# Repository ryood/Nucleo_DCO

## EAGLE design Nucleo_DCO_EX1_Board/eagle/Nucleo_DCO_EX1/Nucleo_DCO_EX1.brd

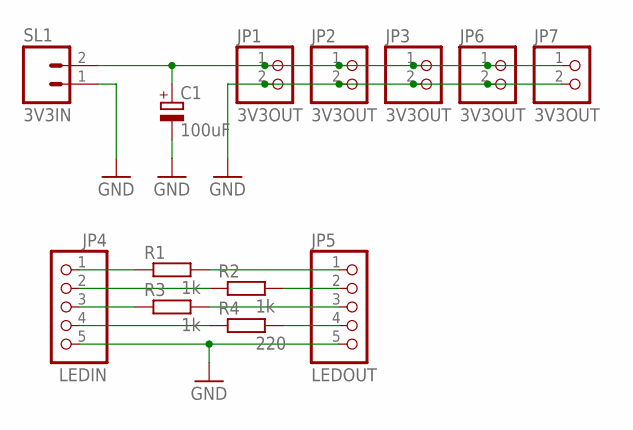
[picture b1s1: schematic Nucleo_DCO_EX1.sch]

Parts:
C1: 100uF; SANYO-OSCON_C6
JP1, JP2, JP3, JP6, JP7: 3V3OUT; 1X02
JP4: LEDIN; 1X05
JP5: LEDOUT; 1X05
R1, R2, R3: 1k; 0207/7
R4: 220; 0207/7
SL1: 3V3IN; 02P

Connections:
GND: C1.-, JP1.2, JP2.2, JP3.2, JP4.5, JP5.5, JP6.2, JP7.2, SL1.1
unnamed: C1.+, JP1.1, JP2.1, JP3.1, JP6.1, JP7.1, SL1.2
unnamed: JP4.1, R1.1
unnamed: JP5.1, R1.2
unnamed: JP4.2, R2.1
unnamed: JP5.2, R2.2
unnamed: JP4.3, R3.1
unnamed: JP5.3, R3.2
unnamed: JP4.4, R4.1
unnamed: JP5.4, R4.2

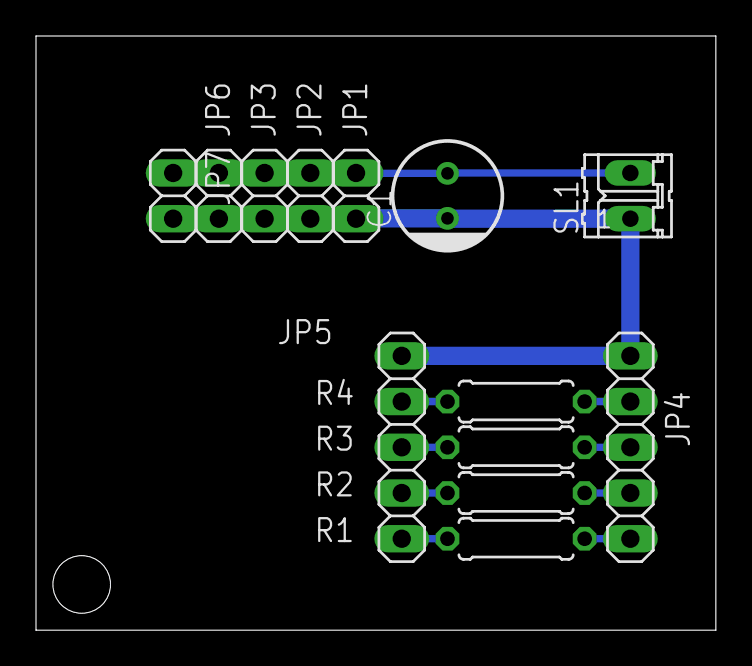
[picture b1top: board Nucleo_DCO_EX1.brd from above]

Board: 2 copper layers, 37.8 x 33.0 mm, 13 parts (0 on the bottom side), 10 nets.

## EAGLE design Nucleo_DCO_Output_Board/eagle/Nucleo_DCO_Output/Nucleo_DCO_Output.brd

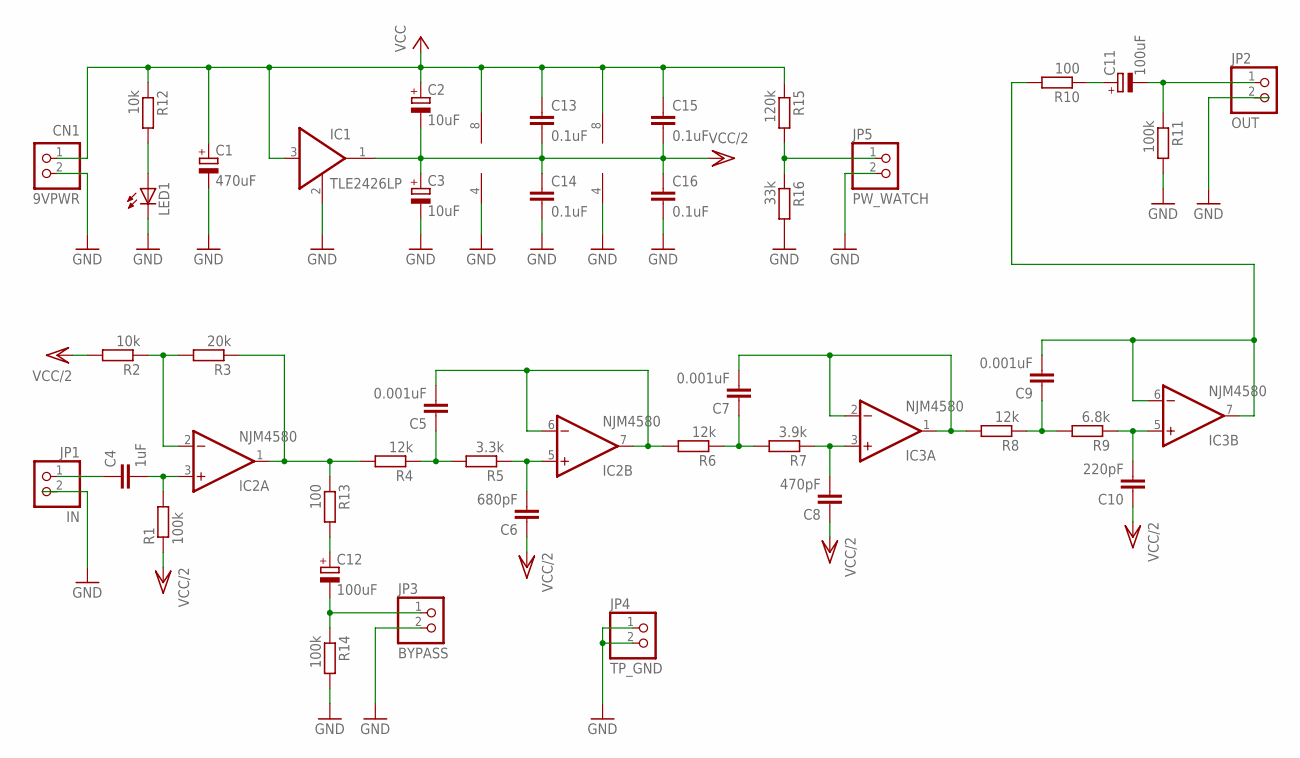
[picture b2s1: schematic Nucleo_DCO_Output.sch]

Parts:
C1: 470uF; SANYO-OSCON_F13
C2, C3: 10uF; E2,5-6
C4: 1uF; C050-035X075
C5, C7, C9: 0.001uF; C050-035X075
C6: 680pF; C050-035X075
C8: 470pF; C050-035X075
C10: 220pF; C050-035X075
C11, C12: 100uF; E5-8,5
C13, C15, C16: 0.1uF; C025-024X044
C14: 0.1uF; C050-024X044
CN1: 9VPWR; B2B-XH-A
IC1: TLE2426LP; TO226AA
IC2, IC3: NJM4580; DIL08
JP1: IN; 1X02
JP2: OUT; 1X02
JP3: BYPASS; 1X02
JP4: TP_GND; 1X02
JP5: PW_WATCH; 1X02
LED1: LED3MM
R1, R11, R14: 100k; 0207/7
R2, R12: 10k; 0207/7
R3: 20k; 0207/7
R4, R6, R8: 12k; 0207/7
R5: 3.3k; 0207/7
R7: 3.9k; 0207/7
R9: 6.8k; 0207/7
R10, R13: 100; 0207/7
R15: 120k; 0207/7
R16: 33k; 0207/7

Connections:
GND: C1.-, C3.-, C14.2, C16.2, CN1.2, IC1.2, IC2.4 (V-), IC3.4 (V-), JP1.2, JP2.2, JP3.2, JP4.1, JP4.2, JP5.2, LED1.K (C), R11.2, R14.2, R16.2
unnamed: IC2.1 (OUT), R3.1, R4.2, R13.1
unnamed: IC2.2 (-IN), R2.1, R3.2
unnamed: C6.2, IC2.5 (+IN), R5.1
unnamed: C4.1, JP1.1
unnamed: C4.2, IC2.3 (+IN), R1.2
unnamed: C5.1, R4.1, R5.2
unnamed: C11.+, R10.1
unnamed: C11.-, JP2.1, R11.1
unnamed: C5.2, IC2.6 (-IN), IC2.7 (OUT), R6.2
unnamed: C8.2, IC3.3 (+IN), R7.1
unnamed: C7.1, R6.1, R7.2
unnamed: LED1.A, R12.2
unnamed: C7.2, IC3.1 (OUT), IC3.2 (-IN), R8.2
unnamed: C10.2, IC3.5 (+IN), R9.1
unnamed: C9.1, R8.1, R9.2
unnamed: C9.2, IC3.6 (-IN), IC3.7 (OUT), R10.2
unnamed: C12.+, R13.2
unnamed: C12.-, JP3.1, R14.1
unnamed: JP5.1, R15.2, R16.1
VCC: C1.+, C2.+, C13.1, C15.1, CN1.1, IC1.3 (I), IC2.8 (V+), IC3.8 (V+), R12.1, R15.1
VCC/2: C2.-, C3.+, C6.1, C8.1, C10.1, C13.2, C14.1, C15.2, C16.1, IC1.1 (O), R1.1, R2.2

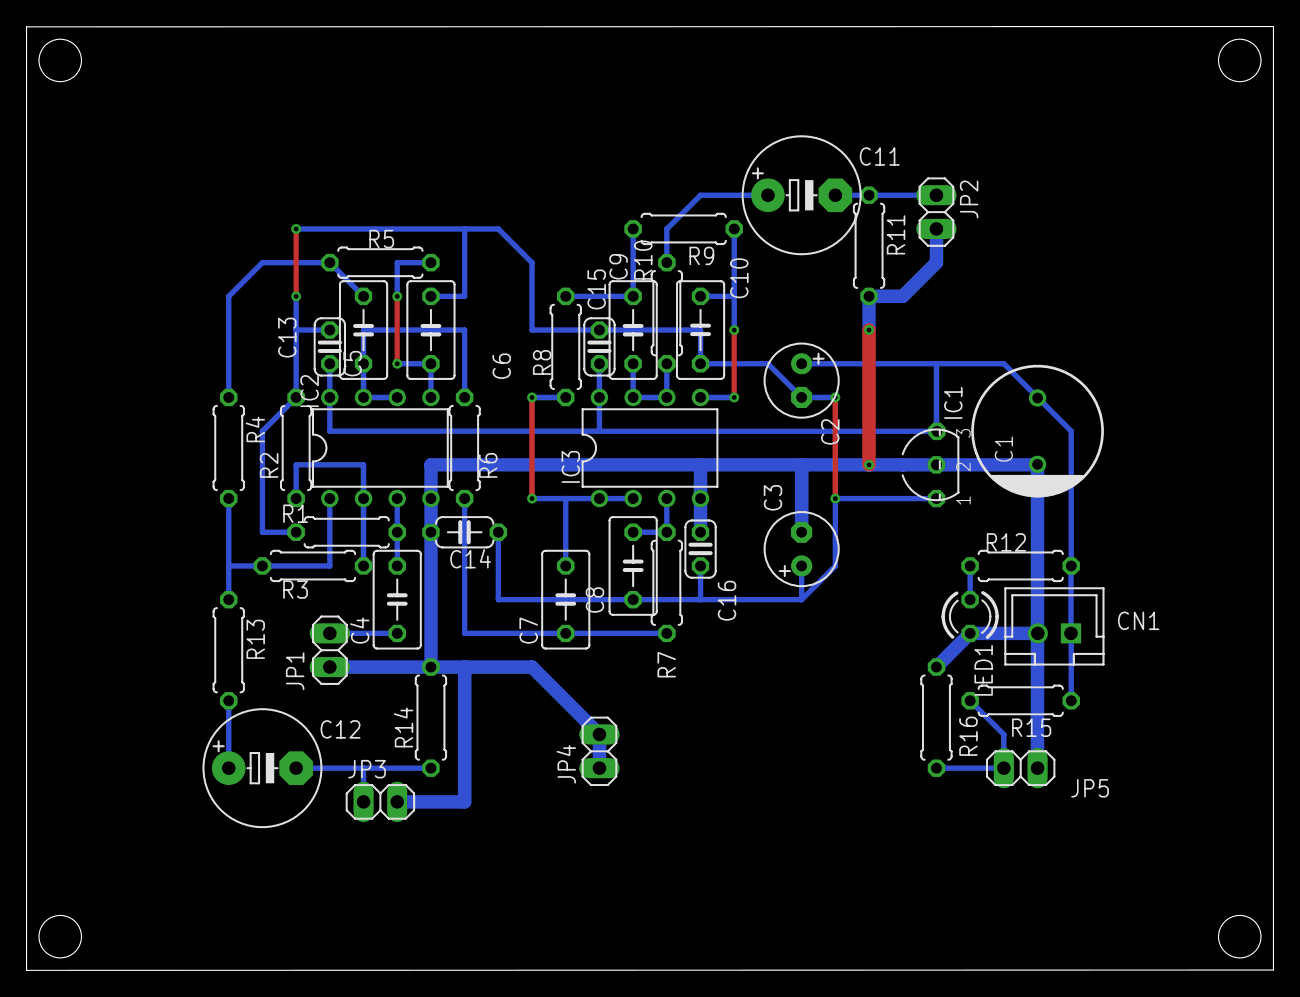
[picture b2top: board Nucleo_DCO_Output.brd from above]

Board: 2 copper layers, 94.0 x 71.1 mm, 42 parts (0 on the bottom side), 22 nets.

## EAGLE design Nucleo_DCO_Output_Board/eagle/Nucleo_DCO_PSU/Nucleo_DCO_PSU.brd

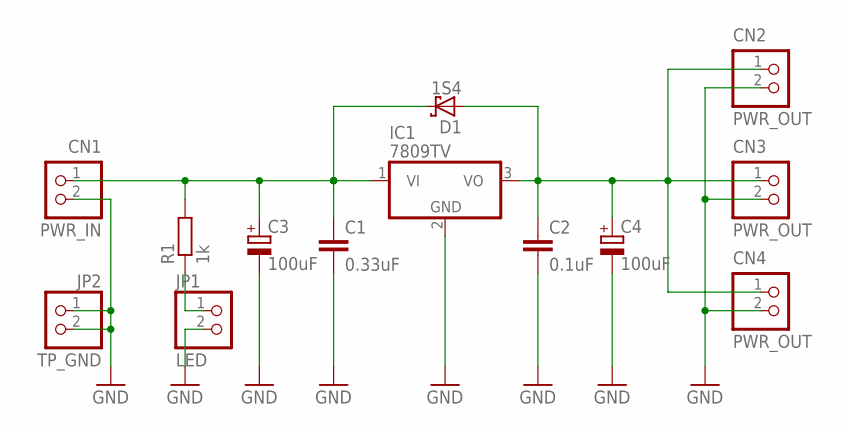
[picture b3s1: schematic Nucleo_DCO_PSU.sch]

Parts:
C1: 0.33uF; C025-024X044
C2: 0.1uF; C025-024X044
C3, C4: 100uF; E5-8,5
CN1: PWR_IN; B2B-XH-A
CN2, CN3, CN4: PWR_OUT; B2B-XH-A
D1: 1S4; DO35-7
IC1: 7809TV; TO220V
JP1: LED; 1X02
JP2: TP_GND; 1X02
R1: 1k; 0207/7

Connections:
GND: C1.2, C2.2, C3.-, C4.-, CN1.2, CN2.2, CN3.2, CN4.2, IC1.2 (GND), JP1.2, JP2.1, JP2.2
unnamed: JP1.1, R1.1
unnamed: C1.1, C3.+, CN1.1, D1.C, IC1.1 (VI), R1.2
unnamed: C2.1, C4.+, CN2.1, CN3.1, CN4.1, D1.A, IC1.3 (VO)

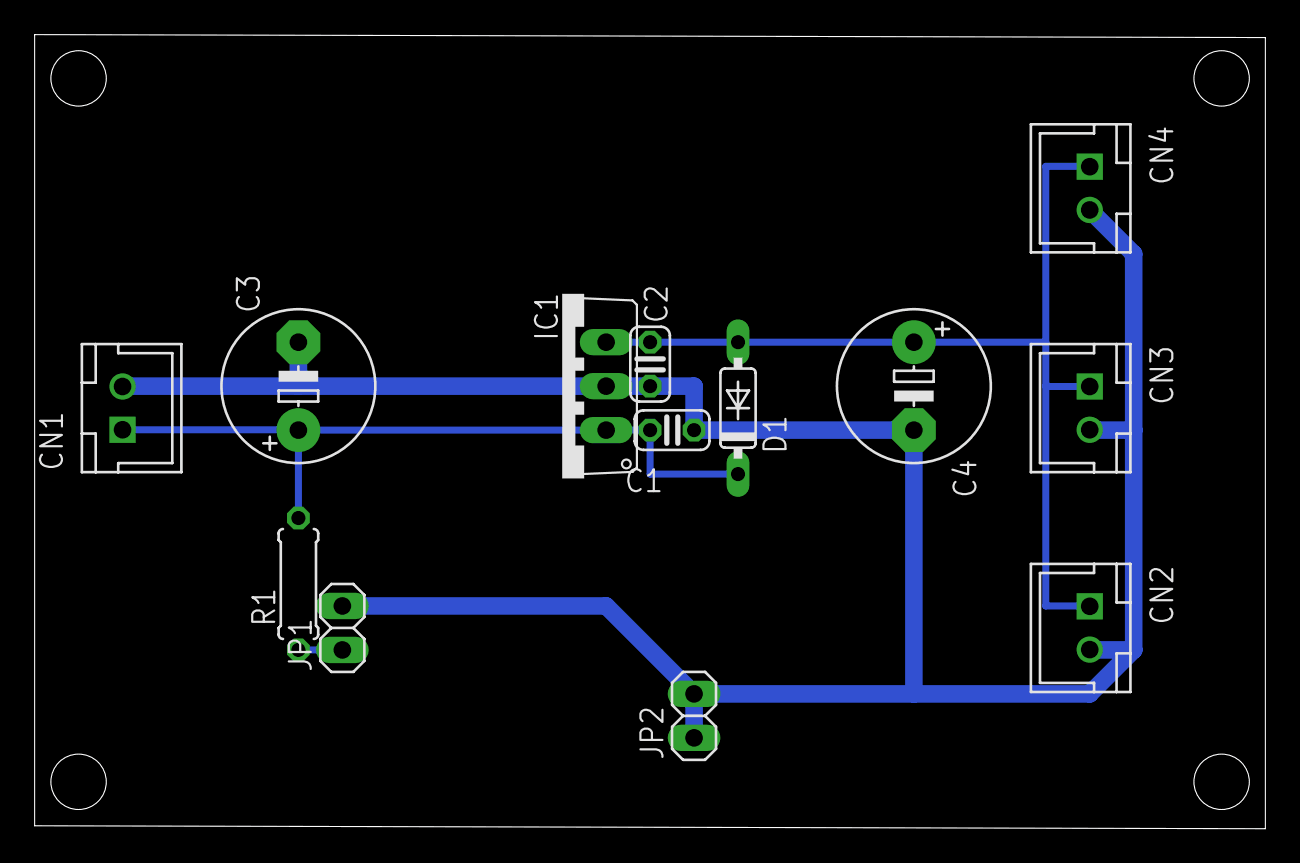
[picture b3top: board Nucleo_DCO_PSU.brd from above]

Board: 2 copper layers, 71.1 x 45.9 mm, 13 parts (0 on the bottom side), 4 nets.

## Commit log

2018-08-19 first commit; Test01
2018-08-19 Add: Visual Studio 2017/GenWaveTable
2018-08-28 Add: Nucleo_DCO_Test02(mbed-cli Project)
2018-08-30 Add: Nucleo_DCO_Test03(DDS Test) Nucleo_DCO_Test04(DDS & u8g2 Test)
2018-08-30 Update: Nucleo_DCO_Test04
2018-08-30 Add: Nucleo_DCO_Test05
2018-08-30 Nucleo_DCO_Test05: succes summing 3 OSC
2018-08-30 In test: Nucleo_DCO_Test05: Amplitude & Phase
2018-09-01 Nucleo_DCO_Test05: Update phase moduration
2018-09-01 Add: Nucleo_DCO_Test06
2018-09-05 Add: MCP3008_Test01, InternalADC_Test01, random_test01, Nucleo_DCO_Test07
2018-09-06 Add: Nucleo_DCO_Test08 (Various waveforms)
2018-09-06 Nucleo_DCO_Test08: Reduce Level POT's resorution
2018-09-06 Nucleo_DCO_Test08: Disable phase change
2018-09-06 Nucleo_DCO_Test08: Impl. noise
2018-09-08 Add: InterruptIn_Test01
2018-09-08 Add: InterruptIn_Test03 (Multi InterruptIn, F767ZI)
2018-09-08 Nucleo_DCO接続一覧表.xlsx
2018-09-08 Update: InterruptIn_Test03
2018-09-08 Add: Nucleo_DCO_Test09 (InterruptIn)
2018-09-08 InterruptIn_Test03: use attach_us()
2018-09-08 Nucleo_DCO_Test09: impl. WaveShape
2018-09-08 Nucleo_DCO_Test09: read
2018-09-08 Nucleo_DCO_Test09: Impl. SQR - pulse width
2018-09-08 Nucleo_DCO_Test09: not use DDS to generate Sawup, Sawdown
2018-09-08 Nucleo_DCO_Test09: Activate phase POT
2018-09-08 Add: Nucleo_DCO_Test10
2018-09-10 Update: Nucleo_DCO_ブロック図
2018-09-11 Add: Pot_Panel_Test01, Pot_Test02
2018-09-11 Add: Nucleo_DCO_Test11 (Frequency Range)
2018-09-11 Update: readme.txt
2018-09-13 Update: Nucleo_DCO接続一覧表
2018-09-13 Nucleo_DCO_Test11: Impl. frequency range
2018-09-13 Nucleo_DCO_Test11: Impl. Master frequency
2018-09-13 Nucleo_DCO_Test11: detuning by pseudo exp. curve
2018-09-13 Ticker -> Timeout for debounce
2018-09-13 Nucleo_DCO_Test11: Impl. Master amplitude.
2018-09-13 Nucleo_DCO_Test11: Increse frequency range
2018-09-13 Add: Nucleo_DCO_Test12 (Increse display mode)
2018-09-13 Nucleo_DCO_Test12: Adjust Debounce Delay
2018-09-13 Update: Nucleo_DCO ブロック図.png
2018-09-13 Add: AverageAnalgoIn_Test01
2018-09-13 Add: InterpolateFloat_Test01
2018-09-13 InterpolateFloat_Test01: multi ADC
2018-09-13 InterpolateFloat_Test01: Clean up
2018-09-13 InterpolateFloat_Test01: Impl. pruning()
2018-09-13 Update: pictures
2018-09-14 Add: doc (Documents)
2018-09-14 Add: FloatingPoint_Test01
2018-09-14 Add: Nucleo_DCO_Test13
2018-09-14 Nucleo_DCO_Test13: Clean up
2018-09-14 Add: Nucleo_DCO_Test14 (Interpolate ADC)
2018-09-14 Nucleo_DCO_Test14: REF_CLOCK=50kHz OK
2018-09-15 Add: Nucleo_DCO_Test15
2018-09-15 Add: RotaryEncoder_Test01
2018-09-15 Add: Nucleo_DCO_Test16
2018-09-15 Nucleo_DCO_Test16: ADC 10bit precision
2018-09-15 Floating_Point_Test01: add, sub
2018-09-17 Nucleo_DCO_Test16 Master Frequency 2 Octave
2018-09-17 Update: Pannel Design
2018-09-17 Update: Nucleo_DCO ブロック図
2018-09-20 Add: ADC_VREF_TEST01
2018-09-20 Update: Panel Design
2018-09-20 Add RotaryEncoder_Test01, RotaryEncoder_Test02
2018-09-20 Add Nucleo_DCO_Test17
2018-09-20 Nucleo_DCO_Test17: Impl PulseWidth Led, Clip Led
2018-09-20 Nucleo_DCO_Test17: UART Trace FPS
2018-09-20 Update: ADC_VREF_TEST01
2018-09-22 Add Nucleo_DCO_Test18
2018-09-22 Nucleo_DCO_Test18 Clean up
2018-09-23 InterruptIn_Test03: Use the panel push switches
2018-09-23 Nucleo_DCO_Test18: Panel switches
2018-09-25 Add Nucleo_DCO_Test19 (ADC Off)
2018-10-01 Nucleo_DCO_Test19: bug fix (pulse width display )
2018-10-01 Add: Nucleo_DCO_Test20
2018-10-01 Nucleo_DCO_Test20: Impl. Thread
2018-10-01 Add: Nucleo_DCO_Test21 (ADC Thread only)
2018-10-03 Test19, Test20, Test21: Serial print ProjectName, time
2018-10-03 Add: Nucleo_DCO_Test19.1
2018-10-06 Add Nucleo_DCO_Test20_Single_Supply_OutputBoard.fzz
2018-10-10 Add: Nucleo_DCO_LPF
2018-10-13 Nucleo_DCO_Output
2018-10-19 Add eagle files
2018-10-22 Nucleo_DCO_PSU
2018-10-22 Update: Nucleo_DCO_Output (add de-coupling cap)
2018-10-27 Nucleo_DCO_Output_Board: Soldering
2018-11-09 Add: I2C_Master_OLED_Test01
2018-11-09 I2C_Master_OLED_Test01: send string ok.
2018-11-09 I2C_Master_OLED_Test01: send TITLE_STR2 ok.
2018-11-09 I2C_Master_OLED_Test01: send TITLE_STR3 NG.
2018-11-09 I2C_Master_OLED_Test01: 文字列の送出を分離
2018-11-09 I2C_Master_OLED_Test01: 文字列の送出を分離（タイミング調整 wait_ms(1)）
2018-11-10 Update: Nucleo_DCO_I2C_Slave_OLED_Test.ino
2018-11-10 Nucleo_DCO_I2C_Slave_OLED_Test: Impl. DM_NORMAL
2018-11-11 Nucleo_DCO_I2C
2018-11-11 Make directory: Nucleo-Arduino_I2C_Test
2018-11-11 Nucleo-Arduino_I2C_Test: UserButton
2018-11-11 Add: Nucleo_DCO_I2C_Slave_OLED_print_Test (user u8g2::print())
2018-11-12 Nucleo-Arduino_I2C_Test: u8g2 FullBuffer
2018-11-17 Nucleo_DCO_Test30
2018-11-17 Update: chassis design
2018-11-17 Update: Top Panel Design (180mm Width)
2018-11-21 Update: Nucleo_DCO_Panel_Design
2018-11-24 Add: Nucleo_DCO_Test23
2018-11-24 Add: RotaryEncoder_Test03
2018-11-26 Add: Nucleo_DCO_EX1 board design
2018-11-26 Nucleo_DCO_Test23: Exchange Leds Pin asign
2018-12-01 Add: Nucleo_DCO 出音テスト
2018-12-01 Update: Panel_Design
2018-12-20 Add: Nucleo_DCO_Test24
2018-12-21 Update: Nucleo_DCO_Test24
